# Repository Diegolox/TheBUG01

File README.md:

# TheBUG01 ⚡

## 🇬🇧 Project Description

<p align="justify">
This project is a custom <strong>all-in-one PCB</strong> for a <strong>two-wheel differential drive robot</strong>, designed to be <strong>plug-and-play</strong> and easy to integrate into new robotics prototypes. The board brings together the key building blocks needed for motion control and autonomous navigation, so you can focus on software and algorithms instead of wiring and power integration.
</p>

### Key Features

* **2-wheel robot control PCB** with integrated peripherals for rapid development.
* **IMU (Inertial Measurement Unit)** for orientation and motion sensing.
* **3× TOF400 laser distance sensors** connected via **I²C**, enabling obstacle detection and basic autonomous navigation.
* **TB6612FNG dual motor driver** for controlling the DC motors efficiently (PWM + direction control).
* **Motor protection circuitry** to handle cases where motors behave like generators (back-EMF / regenerative effects), improving robustness and protecting the power stage.
* **Push buttons** with **RC filtering** and **external pull-up**, providing stable, noise-resistant digital inputs.
* **Test LEDs** for quick debugging and status indication during bring-up.
* **Integrated DC-DC converter** to step down from the **battery voltage** to the robot’s required internal rail(s), simplifying power distribution and improving overall reliability.

### PCB Layout

### Schematic

### Goal

<p align="justify">
The goal of this PCB is to provide a compact robotics platform with <strong>everything integrated</strong>: power regulation, sensing, motor driving, and basic user I/O. With this hardware, you can quickly implement and iterate on:
</p>

* Wheel speed and position control loops
* Differential drive kinematics
* Sensor-based navigation using the TOF lasers
* Autonomous behaviors (obstacle avoidance, wall following, basic SLAM-ready sensing layout)

---

## 🇪🇸 Descripción del proyecto

<p align="justify">
Este proyecto es una <strong>PCB todo-en-uno</strong> para un <strong>robot diferencial de dos ruedas</strong>, pensada para ser <strong>plug-and-play</strong> y facilitar el desarrollo rápido de prototipos. La placa integra los bloques principales necesarios para control de movimiento y navegación autónoma, evitando cableado extra y problemas de integración de potencia.
</p>

### Características principales

* **PCB de control para robot de 2 ruedas** con periféricos integrados para desarrollo rápido.
* **IMU (Unidad de Medición Inercial)** para estimar orientación y movimiento.
* **3× sensores láser de distancia TOF400** por **I²C**, para detección de obstáculos y navegación básica.
* **Driver dual TB6612FNG** para el control eficiente de motores DC (PWM + dirección).
* **Circuitería de protección para motores** cuando actúan como generadores (back-EMF / regeneración), aumentando la robustez y protegiendo la etapa de potencia.
* **Pulsadores** con **filtro RC** y **pull-up externa**, para entradas digitales estables y resistentes al ruido.
* **LEDs de testeo** para depuración rápida y verificación del estado durante el bring-up.
* **Convertidor DC-DC integrado** para bajar la **tensión de baterías** a las líneas internas del robot, simplificando la distribución de potencia.

### Objetivo

<p align="justify">
El objetivo es ofrecer una plataforma compacta con <strong>todo integrado</strong>: regulación de potencia, sensórica, driver de motores y E/S básica. Con este hardware se pueden implementar de forma rápida:
</p>

* Control de velocidad/posición de ruedas
* Cinemática diferencial
* Navegación basada en sensores TOF
* Comportamientos autónomos (evitación de obstáculos, seguimiento de pared, base para SLAM)

---

* **Status:** In development
* **In collaboration with Carlos Rios Ferrer**

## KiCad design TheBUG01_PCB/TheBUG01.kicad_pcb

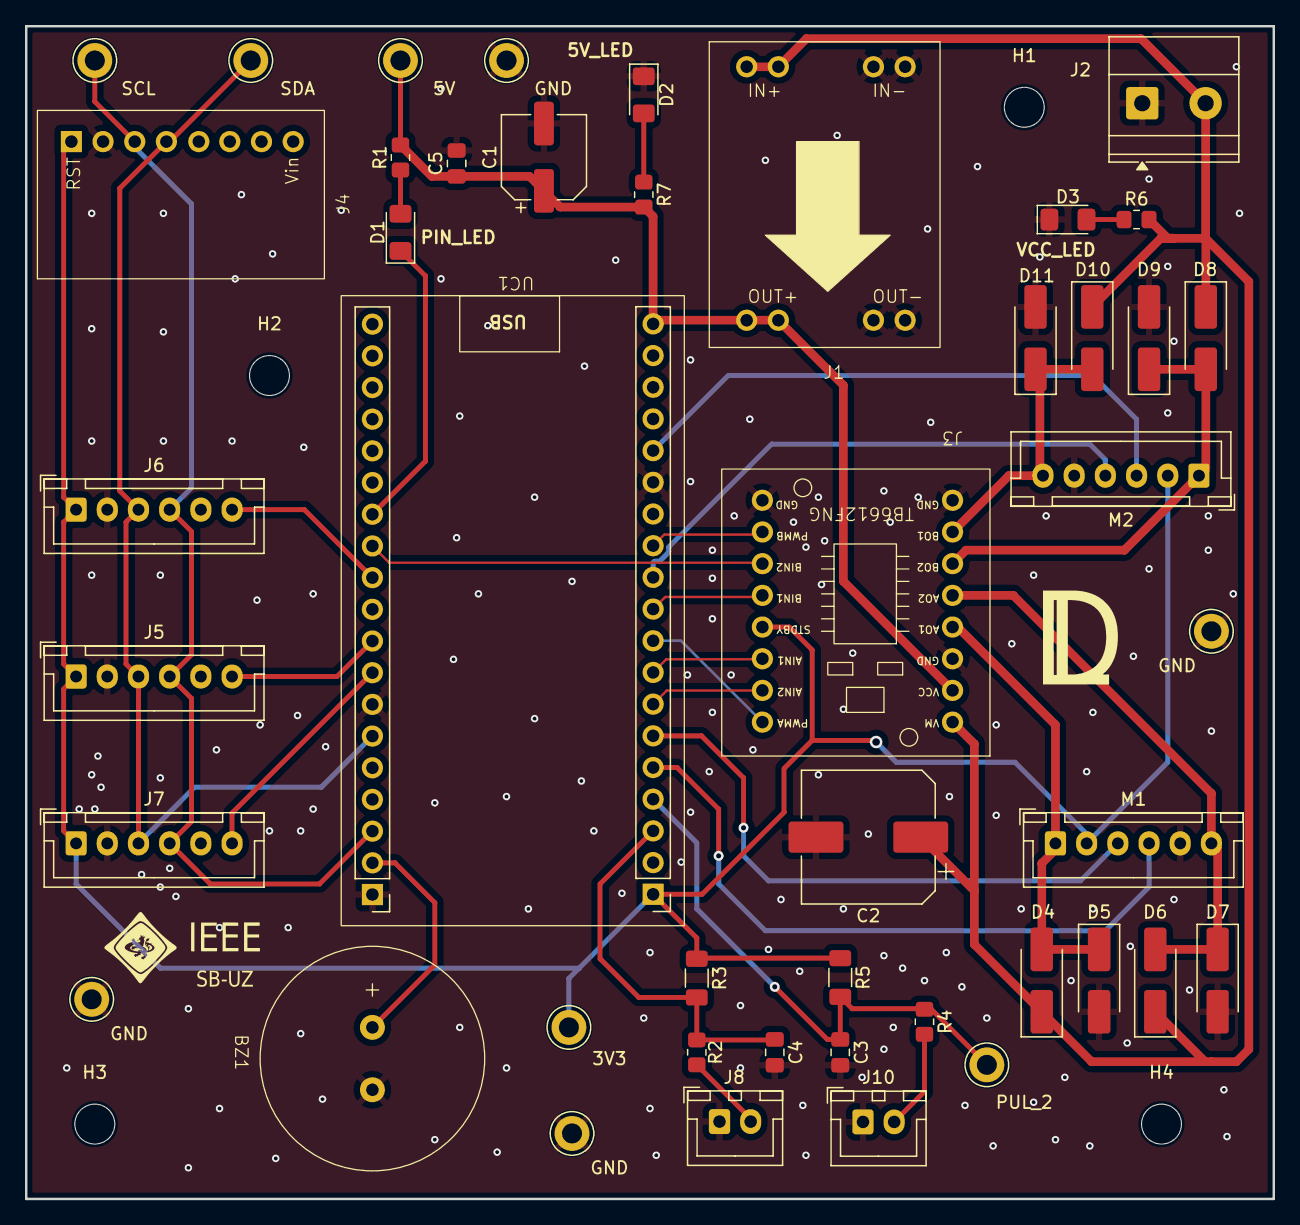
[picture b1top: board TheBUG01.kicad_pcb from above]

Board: 2 copper layers, 100.0 x 94.0 mm, 49 parts (0 on the bottom side), 32 nets.

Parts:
3V3: TEST_3V3; TestPoint_Keystone_5005-5009_Compact
5V: TEST_5V; TestPoint_Keystone_5005-5009_Compact
BZ1: Buzzer; BUZZER
C1: 470uF, 10V; CP_Elec_6.3x7.7
C2: 470uF, 25V; CP_Elec_10x10.5
C3, C4: 1uF; C_0805_2012Metric_Pad1.18x1.45mm_HandSolder
C5: 100nF, 10V; C_0805_2012Metric_Pad1.18x1.45mm_HandSolder
D1: AZUL; LED_1206_3216Metric_Pad1.42x1.75mm_HandSolder
D2: AMARILLO; LED_1206_3216Metric_Pad1.42x1.75mm_HandSolder
D3: ROJO; LED_1206_3216Metric_Pad1.42x1.75mm_HandSolder
D4, D5, D6, D7, D8, D9, D10, D11: M7; D_SMA_Handsoldering
GND: TEST_GND; TestPoint_Keystone_5005-5009_Compact
GND#2, GND#3, GND#4: TEST_GND; TestPoint_Keystone_5005-5009_Compact
H1, H2, H3, H4: MountingHole; MountingHole_3.2mm_M3
J1: MP1584EN 5V; MP1584
J2: ENTRADA ALIM; TerminalBlock_Phoenix_MKDS-1,5-2-5.08_1x02_P5.08mm_Horizont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
J3: DRIVER MOTORES; TB6612FNG
J4: IMU BNO055; BNO055
J5: LÁSER TOF 1; JST_XH_B6B-XH-A_1x06_P2.50mm_Vertical
J6: LÁSER TOF 2; JST_XH_B6B-XH-A_1x06_P2.50mm_Vertical
J7: LÁSER TOF 3; JST_XH_B6B-XH-A_1x06_P2.50mm_Vertical
J8, J10: Conn_01x02; JST_XH_B2B-XH-A_1x02_P2.50mm_Vertical
M1, M2: MOTOR 2; JST_XH_B6B-XH-A_1x06_P2.50mm_Vertical
PUL_2: TEST_GND; TestPoint_Keystone_5005-5009_Compact
R1, R7: 1kohm, 0.1W; R_0805_2012Metric_Pad1.20x1.40mm_HandSolder
R2, R4: 330ohm, 0.75W; R_0805_2012Metric_Pad1.20x1.40mm_HandSolder
R3: 10k, 0.1W; R_1206_3216Metric_Pad1.30x1.75mm_HandSolder
R5: 10k, 0.25W; R_1206_3216Metric_Pad1.30x1.75mm_HandSolder
R6: 2k2ohm, 0.1W; R_0805_2012Metric_Pad1.20x1.40mm_HandSolder
SCL: TEST_GND; TestPoint_Keystone_5005-5009_Compact
SDA: TEST_GND; TestPoint_Keystone_5005-5009_Compact
UC1: ESP32; ESP32_WROOM32_SHIELD_V01

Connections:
+3V3: 3V3.1, J3.11 (STDBY), J4.1 (Vin), J5.1 (Vin), J6.1 (Vin), J7.1 (Vin), M1.2 (VCC_ENC), M2.2 (VCC_ENC), R3.1, R5.1, UC1.1 (3V3)
+5V: 5V.1, C1.1, C5.1, J1.2 (OUT+), J3.1 (VCC), R1.2, R7.2, UC1.19 (5V)
BUZZER: BZ1.1 (+), UC1.21 (GPIO23)
ENC_A_1: M1.3 (ENC_B), UC1.6 (GPIO35)
ENC_A_2: M1.4 (ENC_A), UC1.5 (GPIO34)
ENC_B_1: M2.3 (ENC_B), UC1.15 (GPIO13)
ENC_B_2: M2.4 (ENC_A), UC1.11 (GPIO27)
GND: BZ1.2 (-), C1.2, C2.2, C3.2, C4.2, C5.2, D2.1 (K), D3.1 (K), D5.2 (A), D7.2 (A), D9.2 (A), D11.2 (A), GND.1, GND#2.1, GND#3.1, GND#4.1, J1.1 (IN-), J1.3 (OUT-), J2.1, J3.2 (GND), J3.7 (GND), J3.15 (GND), J4.2 (GND), J5.2 (GND), J6.2 (GND), J7.2 (GND), J8.1, J10.1, M1.5 (GND_ENC), M2.5 (GND_ENC), UC1.14 (GND), UC1.20 (GND), UC1.26 (GND)
IN_A_1: J3.9 (INA_2), UC1.7 (GPIO32)
IN_A_2: J3.10 (INA_1), UC1.8 (GPIO33)
IN_B_1: J3.12 (INB_1), UC1.10 (GPIO26)
IN_B_2: J3.13 (INB_2), UC1.31 (GPIO16)
MOT_A_1: D4.2 (A), D5.1 (K), J3.3 (Aout1), M1.1 (MOT-)
MOT_A_2: D6.2 (A), D7.1 (K), J3.4 (Aout2), M1.6 (MOT+)
MOT_B_1: D8.2 (A), D9.1 (K), J3.5 (Bout1), M2.1 (MOT-)
MOT_B_2: D10.2 (A), D11.1 (K), J3.6 (Bout2), M2.6 (MOT+)
unnamed: D1.2 (A), R1.1
unnamed: D2.2 (A), R7.1
unnamed: D3.2 (A), R6.1
unnamed: J8.2, R2.2
unnamed: J10.2, R4.2
PIN_LED: D1.1 (K), UC1.32 (GPIO04)
PIN_PULSADOR_1: C4.1, R2.1, R3.2, UC1.3 (GPIO36)
PIN_PULSADOR_2: C3.1, PUL_2.1, R4.1, R5.2, UC1.4 (GPIO39)
PWM_A: J3.8 (PWM_A), UC1.9 (GPIO25)
PWM_B: J3.14 (PWM_B), UC1.12 (GPIO14)
SCL: J4.3 (SCL/Rx), J5.4 (SCL), J6.4 (SCL), J7.4 (SCL), SCL.1, UC1.22 (GPIO22)
SDA: J4.4 (SDA/Tx), J5.3 (SDA), J6.3 (SDA), J7.3 (SDA), SDA.1, UC1.25 (GPIO21)
SHUT_LAS_1: J5.6 (SHUT), UC1.28 (GPIO18)
SHUT_LAS_2: J6.6 (SHUT), UC1.30 (GPIO17)
SHUT_LAS_3: J7.6 (SHUT), UC1.27 (GPIO19)
VCC: C2.1, D4.1 (K), D6.1 (K), D8.1 (K), D10.1 (K), J1.0 (IN+), J2.2, J3.0 (VM), R6.2

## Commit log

2026-03-04 Enhance README with project details and features
    Added detailed project description, key features, and goals in both English and Spanish.
2026-03-04 PCB_PROYECT
2026-03-04 boom
2026-03-04 SCH_PDF
2026-03-04 PCB_FRONT_AND_BACK_PLANS
2026-03-06 Rename BOOM_TheBUG01.xlsx to docs/BOOM_TheBUG01.xlsx
2026-03-06 Rename ESP_SHIELD_4-B_Cu.pdf to docs/ESP_SHIELD_4-B_Cu.pdf
2026-03-06 Rename ESP_SHIELD_4-F_Cu.pdf to docs/ESP_SHIELD_4-F_Cu.pdf
2026-03-06 Rename SCH_TheBUG01.pdf to docs/SCH_TheBUG01.pdf
2026-03-06 Add 3D image to README for better visualization
    Added a 3D visualization image to the project description.
2026-03-06 Add PCB layout and schematic sections to README
    Added sections for PCB layout and schematic images.
2026-03-06 Update README with status and collaboration info
    Added additional status details and collaboration information.
2026-03-09 Update README with project title and description
    Add project title and enhance README description.
2026-03-09 Fix header formatting in README.md
    Added a space after the header for better formatting.
